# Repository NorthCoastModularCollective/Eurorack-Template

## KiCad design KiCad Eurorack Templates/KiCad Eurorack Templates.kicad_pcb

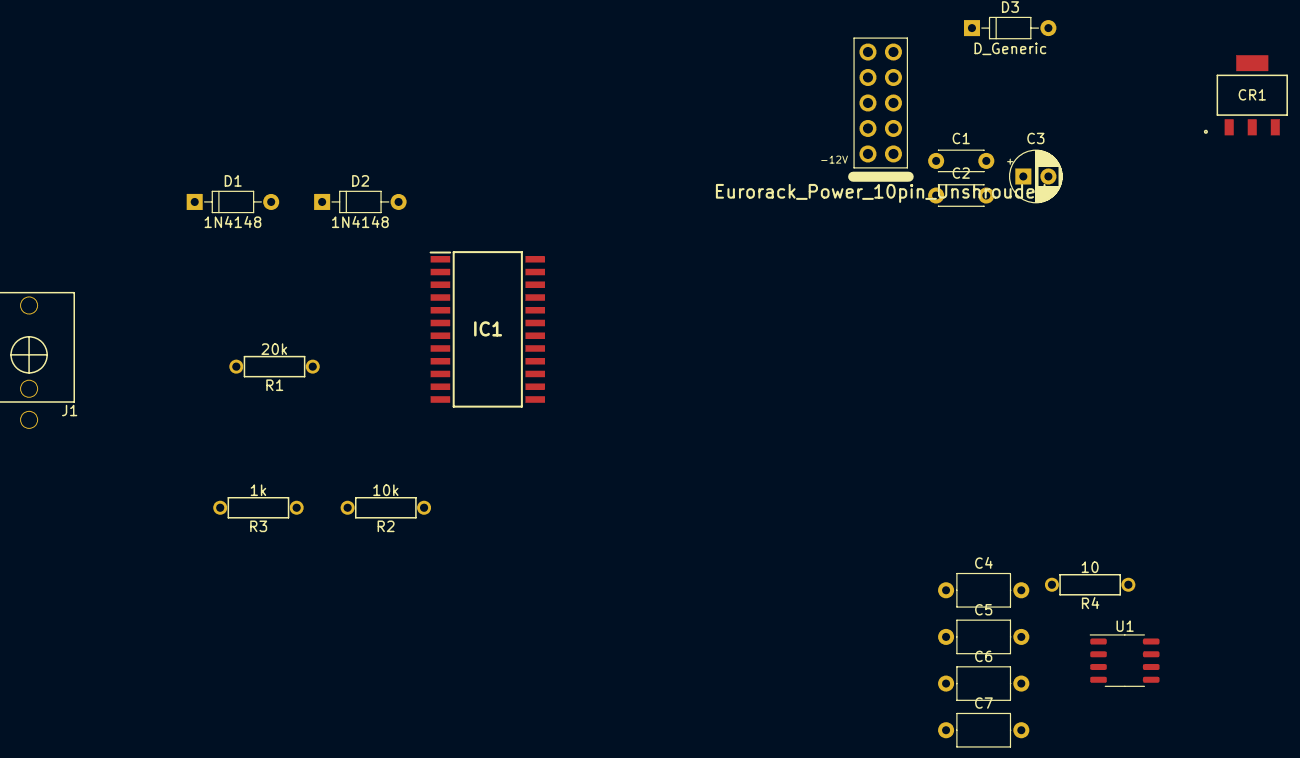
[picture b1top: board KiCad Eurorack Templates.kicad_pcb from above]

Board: 2 copper layers, 19 parts (0 on the bottom side), 11 nets, no tracks yet.

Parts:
C1, C2: 10uF; C_Disc_D4.3mm_W1.9mm_P5.00mm
C3: 22uF; CP_Radial_D5.0mm_P2.50mm
C4, C6, C7: 47uF; C_Axial_L5.1mm_D3.1mm_P7.50mm_Horizontal
C5: 0.1uF; C_Axial_L5.1mm_D3.1mm_P7.50mm_Horizontal
CR1: LD1117S50CTR; SOT-223_STM
D1, D2: 1N4148; D_DO-35_P7.62mm_Horizontal
D3: D_Generic; D_DO-35_P7.62mm_Horizontal
IC1: CD74HCT4067M; SOIC127P1030X265-24N
J1: 3.5mm_Mono_Switched; PJ301M-12
J2: Eurorack_Power_10pin_Unshrouded; Pins_2x05_2.54mm_TH_Europower
R1: 20k; R_Axial_DIN0207_L6.3mm_D2.5mm_P7.62mm_Horizontal
R2: 10k; R_Axial_DIN0207_L6.3mm_D2.5mm_P7.62mm_Horizontal
R3: 1k; R_Axial_DIN0207_L6.3mm_D2.5mm_P7.62mm_Horizontal
R4: 10; R_Axial_DIN0207_L6.3mm_D2.5mm_P7.62mm_Horizontal
U1: PT8211; SOP-8_3.9x4.9mm_P1.27mm

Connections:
+3.3V: IC1.24 (VCC), R4.1
+5V: C2.1, CR1.2 (VOUT)
+12V: C1.1, C3.1, CR1.3 (VIN), D3.1 (K)
GND: C1.2, C2.2, C3.2, C4.2, C5.2, CR1.1 (ADJ/GND), IC1.12 (GND), IC1.15 (~E), J1.1 (SHEILD), J1.2 (SW), J2.3 (GND), J2.5 (GND), J2.7 (GND), R2.1, U1.4 (GND)
unnamed: D1.2 (A), J1.3 (SIG)
unnamed: D1.1 (K), R1.1
unnamed: D2.2 (A), R1.2, R2.2, R3.1
unnamed: D3.2 (A), J2.2 (+12V)
unnamed: C7.1, U1.6 (LCH)
unnamed: C6.1, U1.8 (RCH)
unnamed: C4.1, C5.1, R4.2, U1.5 (VDD)

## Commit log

2024-02-07 Added initial KiCad template files
2024-02-07 added gitignore
